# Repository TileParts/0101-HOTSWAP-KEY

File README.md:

0101-HOTSWAP-KEY
==========

一个机械键盘热插拔轴座的转接板。

## 协议

[CERN-OHL-P-2.0](LICENSE)

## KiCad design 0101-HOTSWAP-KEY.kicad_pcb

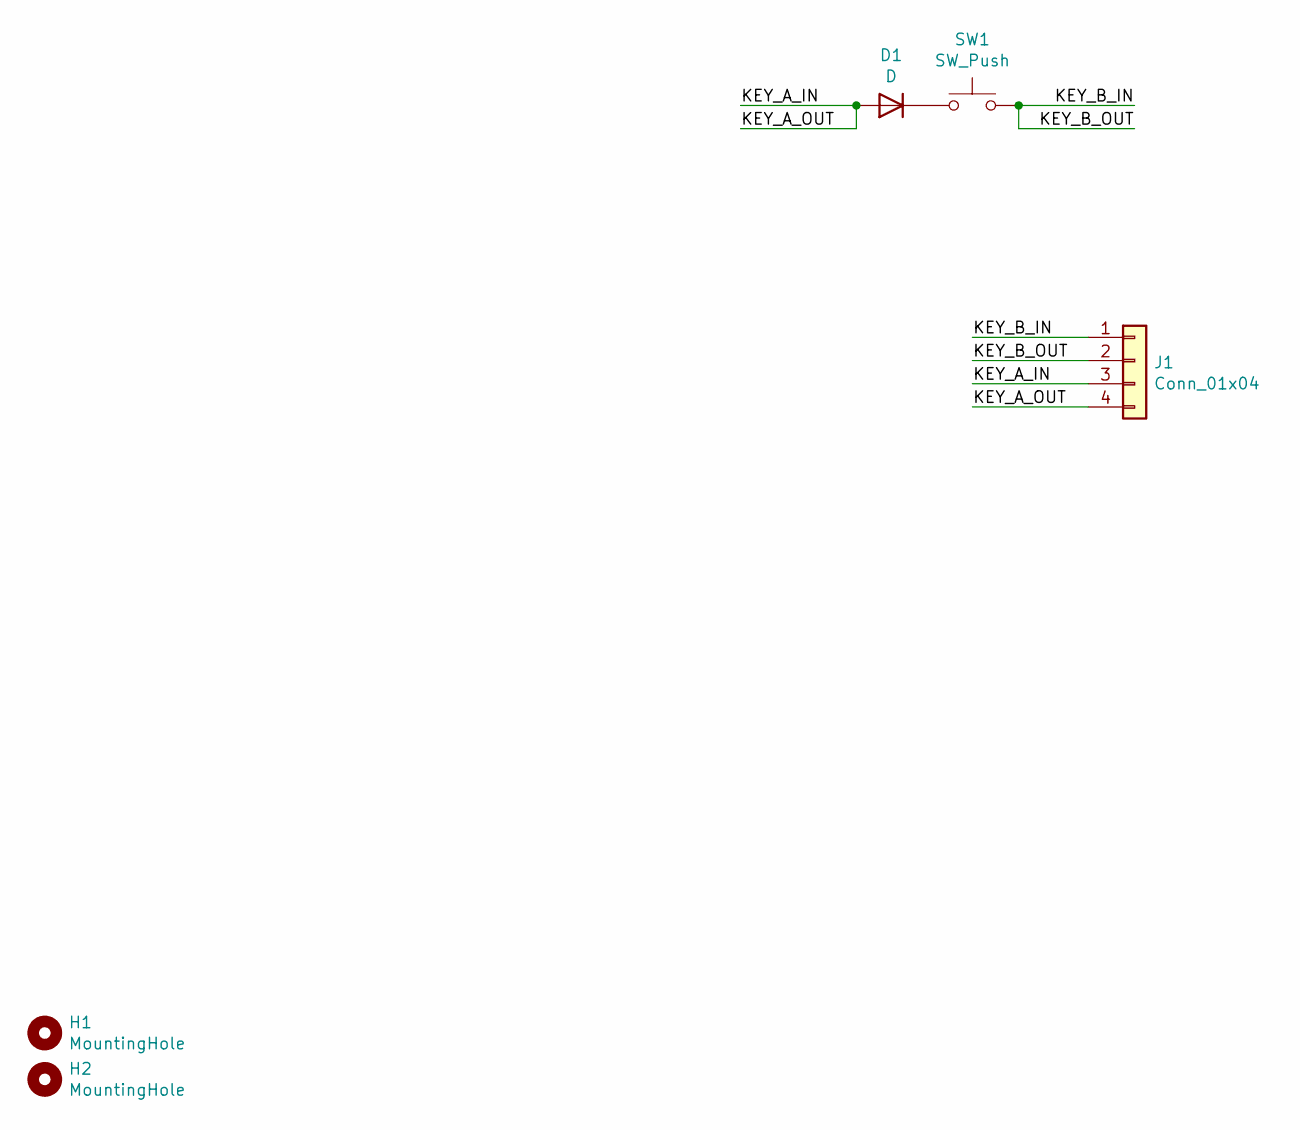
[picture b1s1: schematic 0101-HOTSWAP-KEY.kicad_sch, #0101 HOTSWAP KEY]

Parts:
D1: D; D_SOD-123; PartNumber C179717
H1, H2: MountingHole; MountingHole_2.2mm_M2
J1: Conn_01x04; PinHeader_1x04_P2.54mm_Horizontal_SMD
SW1: SW_Push; SW_Hotswap_Kailh_MX_1.00u; PartNumber C2803348

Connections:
/KEY_A_IN: D1.2 (A), J1.3, J1.4
/KEY_B_IN: J1.1, J1.2, SW1.1
unnamed: D1.1 (K), SW1.2

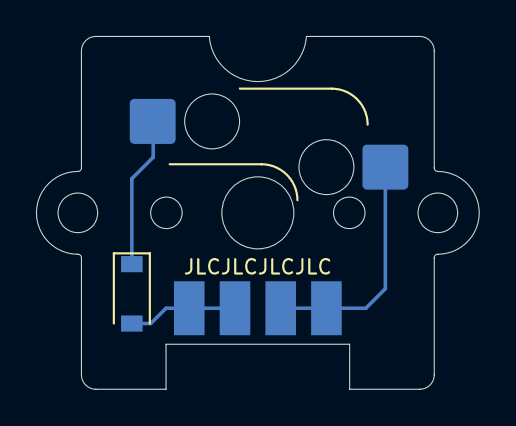
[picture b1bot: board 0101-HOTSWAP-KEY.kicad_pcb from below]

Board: 2 copper layers, 24.6 x 19.6 mm, 11 parts (2 on the bottom side), 3 nets.

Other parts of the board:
kibuzzard-631DE0D4: G***; kibuzzard-631DE0D4
kibuzzard-631DE0DB: G***; kibuzzard-631DE0DB
kibuzzard-631DE0E9: G***; kibuzzard-631DE0E9
kibuzzard-631DE0FD: G***; kibuzzard-631DE0FD
kibuzzard-631DE1A7: G***; kibuzzard-631DE1A7
kibuzzard-631DE163: G***; kibuzzard-631DE163

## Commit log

2022-09-09 Init repository
2022-09-09 Add #0101 HOTSWAP KEY
2022-09-11 Migrate to KiCad 6
2022-09-11 Use kibuzzard silks
2022-09-12 Update PCB settings
2022-09-12 Output gerber V1.0
2022-09-12 Add README
